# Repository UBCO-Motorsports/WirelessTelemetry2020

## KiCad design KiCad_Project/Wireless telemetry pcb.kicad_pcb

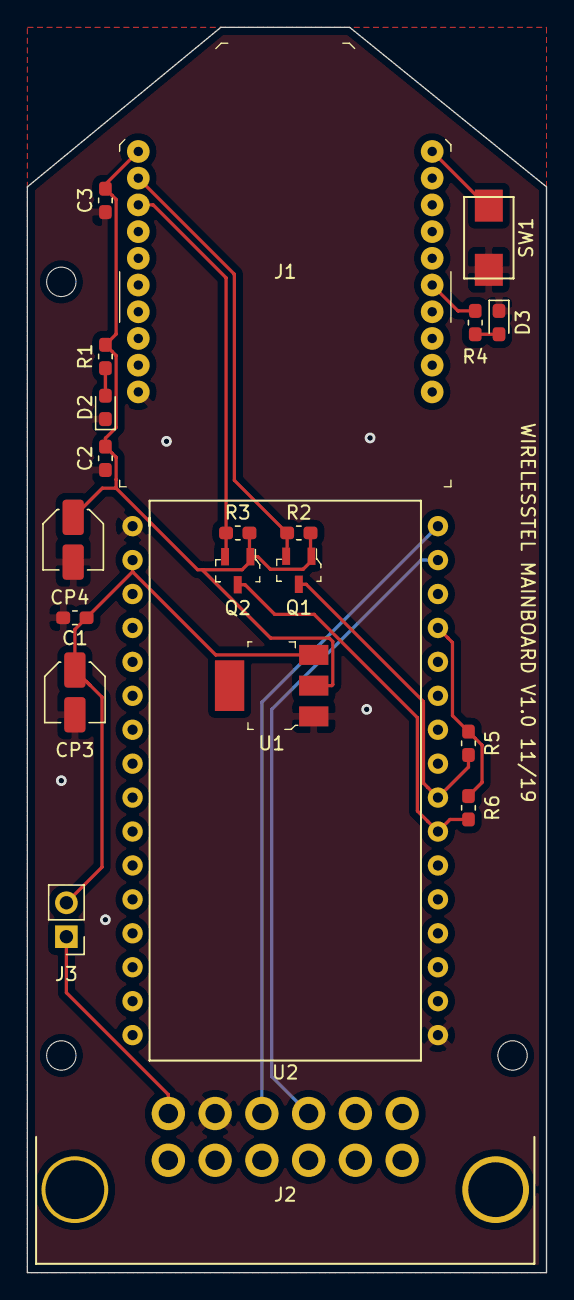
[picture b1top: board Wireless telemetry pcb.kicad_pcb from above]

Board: 2 copper layers, 38.9 x 93.2 mm, 21 parts (0 on the bottom side), 15 nets.

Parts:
C1, C2: 10nF; C_0603_1608Metric_Pad1.05x0.95mm_HandSolder
C3: 8.2pF; C_0603_1608Metric_Pad1.05x0.95mm_HandSolder
CP3, CP4: 10uF; C_Elec_4x5.4
D2, D3: LED; LED_0603_1608Metric_Pad1.05x0.95mm_HandSolder
J1: Conn_02x10_Counter_Clockwise; XBEE_PRO-20_THT
J2: Conn_02x06_Counter_Clockwise; MX120G
J3: Conn_01x02_Male; PinHeader_1x02_P2.54mm_Vertical
Q1, Q2: BSS138; SOT-23-3
R1, R4: 1k; R_0603_1608Metric_Pad1.05x0.95mm_HandSolder
R2, R3, R5, R6: 10k; R_0603_1608Metric_Pad1.05x0.95mm_HandSolder
SW1: SW_Push; PTS636 SK25F SMTR LFS
U1: LD1117V33; SOT-223
U2: ControllerBoardV1; Breadboard_Center_32pin

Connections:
+12V: C1.1, CP3.1, J3.2, U1.3, U2.2
AD0\DIO0\CommissioningPushbutton: J1.20, SW1.1
Associate\DIO5\AD5: J1.15, R4.1
DIN: J1.3, Q2.2, R3.2
DOUT: J1.2, Q1.2, R2.2
GND: C1.2, C2.2, C3.1, CP3.2, CP4.2, D2.1, D3.1, J1.10, J2.2, SW1.2, U1.1, U2.1, U2.32
IN: Q2.3, R6.2, U2.26
unnamed: D2.2, R1.2
unnamed: D3.2, R4.2
unnamed: J2.1, J3.1
unnamed: J2.3, U2.17
unnamed: J2.4, U2.18
OUT: Q1.3, R5.2, U2.25
Vcc3.3V: C2.1, C3.2, CP4.1, J1.1, Q1.1, Q2.1, R1.1, R2.1, R3.1, U1.2
Vcc5V: R5.1, R6.1, U2.20

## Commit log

2019-11-21 KiCad PCB files
    These are the pcb files for the transmitter on the car using the arm nxp chip and xbee modules
2019-11-21 Standardized folder name and added folder for S32DS project
2019-11-21 Added .DS_Store to ignore for Mac
2019-11-21 Added mounting holes and silkscreen
2019-11-22 Added Base S32DS Project
2019-11-22 Few tiny changes before ordering
2019-11-22 Removed .DS_Store
2019-11-23 Added TelemetryViewer
    Added the basic telemetry viewer so we can add more graphs and fields to update car settings.
2019-11-29 Updated Schematics
2020-01-21 Pushed copy of ControlBoard_Core
2020-02-04 Refresh and more
2020-02-04 Finished almost...
    Only thing that needs to be changed is the controls region to add supported commands as they are created.
2020-02-18 Wireless Telemetry Working
2020-02-21 Added Runnable Application File
    Application file added so eclipse isn't needed to run the software anymore. Feel free to download and use for testing. This file will be updated less frequently and only every couple changes or so be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
2020-03-24 Telem Update
    -It just works edition
    added popup option for open layout and changed dependacy on com port number for layout
2020-03-24 Another update
2020-03-24 Small changes
    Updated help tab and file structure
2020-04-08 Telem Version Update to V1.2
    Loading Screen
2020-04-13 V1.2
